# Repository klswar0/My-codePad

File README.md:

# My-codePad
A streamdeck alternative with 1 rotary encoder, oled screen, LEDS!!! and (hopefully) 8 buttons
I real dont know what im doing with hardware so let see what i come up with

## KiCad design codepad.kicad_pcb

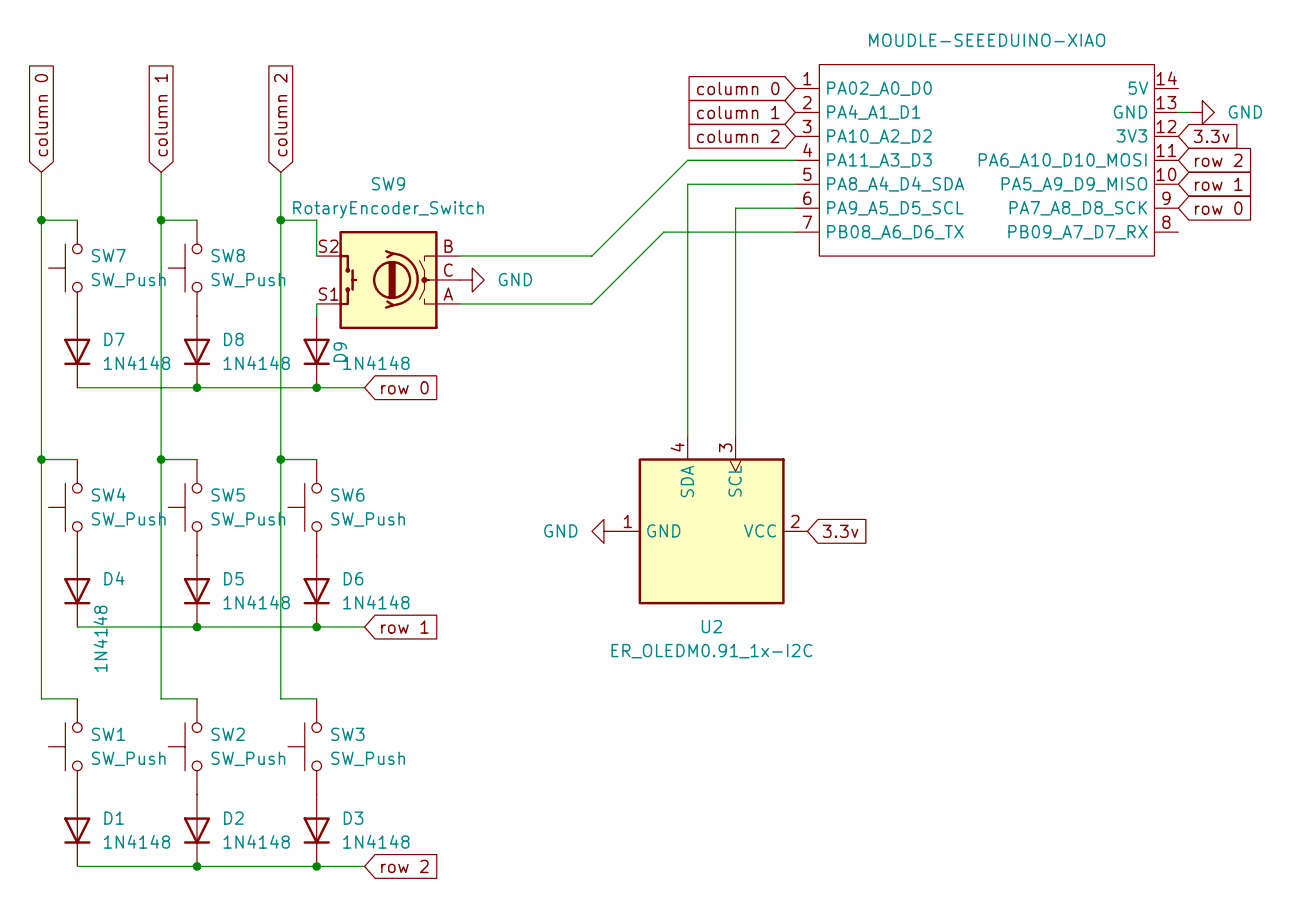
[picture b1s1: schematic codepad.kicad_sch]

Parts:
D1, D2, D3, D4, D5, D6, D7, D8, D9: 1N4148; D_DO-35_SOD27_P7.62mm_Horizontal
SW1, SW2, SW3, SW4, SW5, SW6, SW7, SW8: SW_Push; SW_Cherry_MX_1.00u_PCB
SW9: RotaryEncoder_Switch; RotaryEncoder_Alps_EC11E-Switch_Vertical_H20mm
U1: MOUDLE-SEEEDUINO-XIAO; XIAO-Generic-Hybrid-14P-2.54-21X17.8MM
U2: ER_OLEDM0.91_1x-I2C

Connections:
3.3v: U1.12 (3V3), U2.2 (VCC)
GND: SW9.C, U1.13 (GND), U2.1 (GND)
unnamed: D1.2 (A), SW1.1
unnamed: D2.2 (A), SW2.1
unnamed: D3.2 (A), SW3.1
unnamed: D4.2 (A), SW4.1
unnamed: D5.2 (A), SW5.1
unnamed: D6.2 (A), SW6.1
unnamed: D7.2 (A), SW7.1
unnamed: D8.2 (A), SW8.1
unnamed: D9.2 (A), SW9.S1
unnamed: U1.5 (PA8_A4_D4_SDA), U2.4 (SDA)
unnamed: U1.6 (PA9_A5_D5_SCL), U2.3 (SCL)
unnamed: SW9.B, U1.4 (PA11_A3_D3)
unnamed: SW9.A, U1.7 (PB08_A6_D6_TX)
column 0: SW1.2, SW4.2, SW7.2, U1.1 (PA02_A0_D0)
column 1: SW2.2, SW5.2, SW8.2, U1.2 (PA4_A1_D1)
column 2: SW3.2, SW6.2, SW9.S2, U1.3 (PA10_A2_D2)
row 0: D7.1 (K), D8.1 (K), D9.1 (K), U1.9 (PA7_A8_D8_SCK)
row 1: D4.1 (K), D5.1 (K), D6.1 (K), U1.10 (PA5_A9_D9_MISO)
row 2: D1.1 (K), D2.1 (K), D3.1 (K), U1.11 (PA6_A10_D10_MOSI)

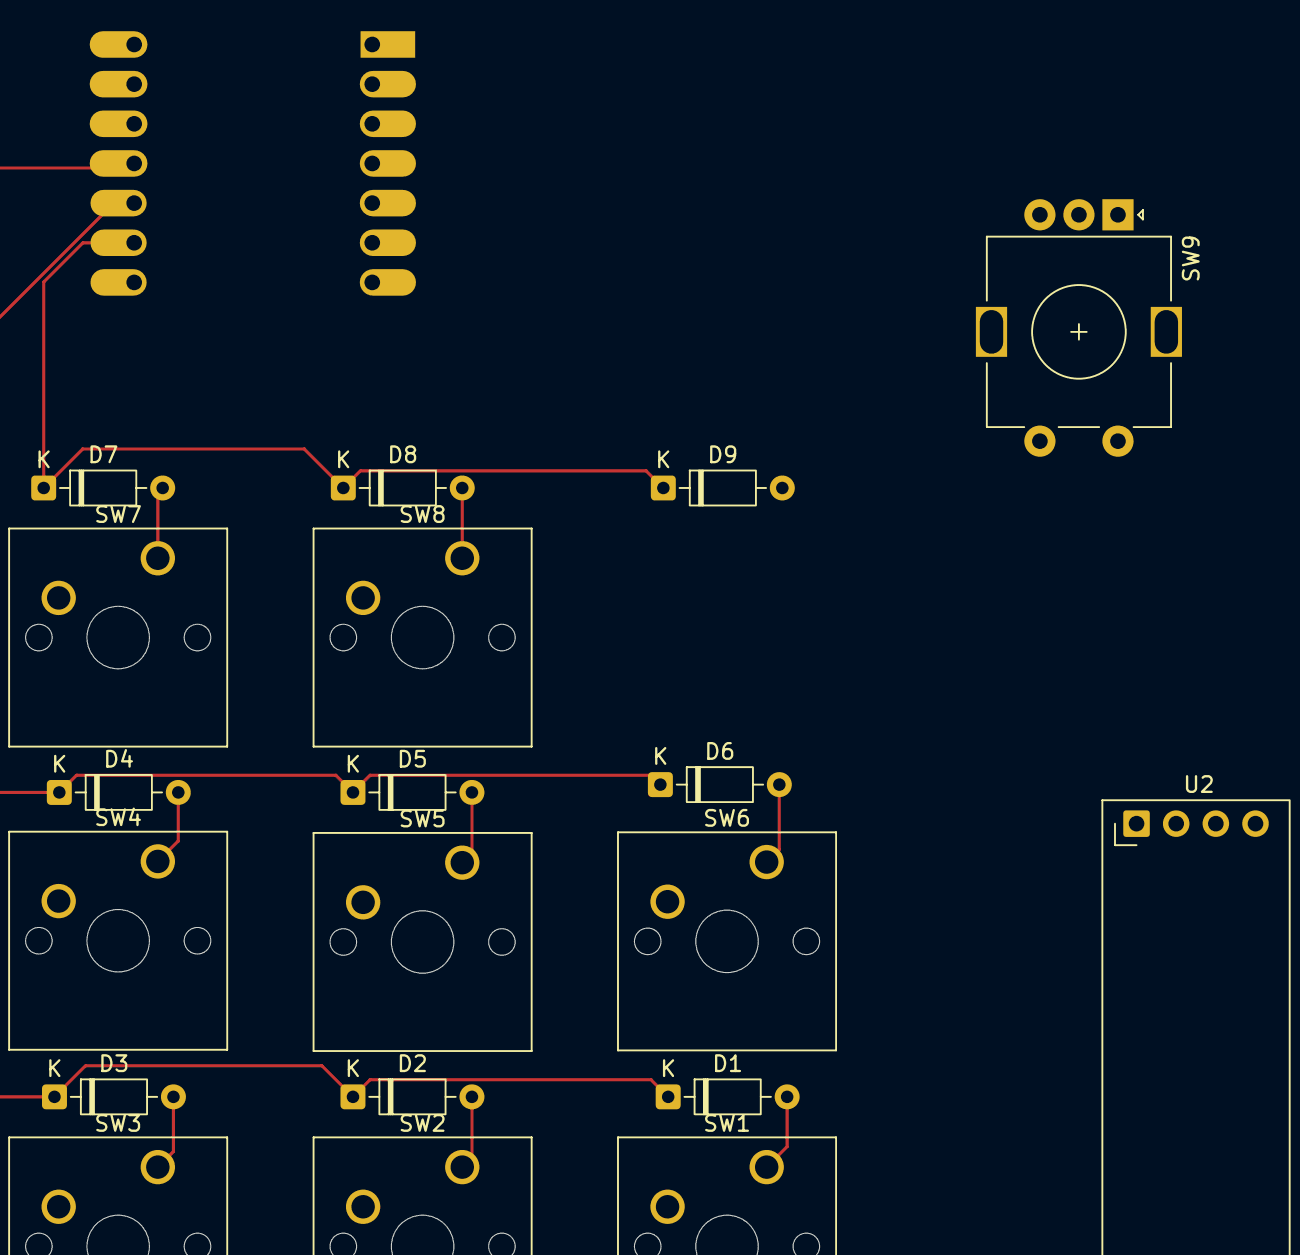
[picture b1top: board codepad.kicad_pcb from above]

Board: 2 copper layers, 20 parts (1 on the bottom side), 21 nets.
